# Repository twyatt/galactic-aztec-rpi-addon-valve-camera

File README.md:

# About

Custom Raspberry Pi Add-on board used for launching the [Galactic Aztec] rocket. The board was designed to be stackable with other add-on boards via the designated [pin configuration].

The Camera Control ethernet port was designed to activate [HackHD] cameras via the [Galactic Aztec Camera Control] \(rev2 or newer) board and can be configured to activate multiple [HackHD]s using the [Galactic Aztec Camera Control Splitter] board.

The Valve Feedback ethernet port was designed to read valve actuation status (open or close) by means of reading Reed switches (for the Main, LOX and Kerosene valves) via the [Galactic Aztec Reed Switch Interface] and [Galactic Aztec Reed Switch Splitter] boards.

Custom EagleCAD parts on this board can be found in the [SDSU Rocket Eagle Libraries].

## Wiring
The Camera Control and Valve Feedback ethernet ports adhered to the following [T-568B] wiring configurations:

### Camera Control
| Pin | Color        | Function |
|:---:|:------------:|:--------:|
| 1   | Orange/White | In       |
| 2   | Orange       | Out      |
| 3   | Green/White  | In       |
| 4   | Blue         | Out      |
| 5   | Blue/White   | In       |
| 6   | Green        | Out      |
| 7   | Brown/White  | In       |
| 8   | Brown        | Out      |

*In and Out do not have a polarity but rather are labeled to distinguish the two sides of the camera connection (used to [control the HackHD] by means of connecting `Button Input` to `Ground`).*

### Valve Feedback
| Pin | Color        | Function |
|:---:|:------------:|:--------:|
| 1   | Orange/White | Main     |
| 2   | Orange       | Main     |
| 3   | Green/White  | LOX      |
| 4   | Blue         | 3.3V     |
| 5   | Blue/White   | 3.3V     |
| 6   | Green        | LOX      |
| 7   | Brown/White  | Kerosene |
| 8   | Brown        | Kerosene |

# Bill of Materials
| Qty | Description                             | Part Number          | Vendor   |
|:---:|-----------------------------------------|---------------------:|----------|
| 1   | Header Stacking 2x20 Tall 23mm          | [1979]               | Adafruit |
| 2   | Jack RJ45 CAT5/CAT5e                    | [380-1046-ND]        | DigiKey  |
| 2   | Header JST PH 2mm 2-pos Right Angle PTH | [455-1719-ND]        | DigiKey  |
| 1   | LED Red Vf=1.8V If=2mA 0603             | [475-1195-2-ND]      | DigiKey  |
| 1   | Molex Mini Fit Jr. 4-pos Right Angle    | [WM1352-ND]          | DigiKey  |
| 1   | LED Red Vf=2V If=20mA 0603              | [754-1359-1-ND]      | DigiKey  |
| 3   | Transistor NPN 40V 600mA SOT-23-3       | [MMBT2222ATPMSCT-ND] | DigiKey  |
| 1   | Resistor 1.8kΩ 1/4W 1% 0603             | [P1.8KBYCT-ND]       | DigiKey  |
| 1   | Resistor 1.2kΩ 2W 1% 2512               | [A116034CT-ND]       | DigiKey  |
| 3   | Resistor 1kΩ 1/4W 1% 0603               | [RHM1.00KADCT-ND]    | DigiKey  |
| 3   | Diode 50V 1A SOD-123                    | [SM4001PL-TPMSCT-ND] | DigiKey  |
| 3   | Relay 5V 5A SPST-NO (1 Form A)          | [Z945-ND]            | DigiKey  |

[Galactic Aztec]: http://rocket.sdsu.edu/rockets
[pin configuration]: https://docs.google.com/spreadsheets/d/1zGslKhH-ZteeA8sbbTjQlF-Neb-wJ3quIlFH6I8Cvgs/edit?usp=sharing
[HackHD]: http://hackhd.com/
[Galactic Aztec Camera Control]: https://github.com/twyatt/galactic-aztec-camera-control
[Galactic Aztec Camera Control Splitter]: https://github.com/twyatt/galactic-aztec-camera-control-splitter
[Galactic Aztec Reed Switch Interface]: https://github.com/twyatt/galactic-aztec-reed-switch-interface
[Galactic Aztec Reed Switch Splitter]: https://github.com/twyatt/galactic-aztec-reed-switch-splitter
[SDSU Rocket Eagle Libraries]: https://github.com/twyatt/SDSURocket-Eagle-Libraries
[T-568B]: https://en.wikipedia.org/wiki/TIA/EIA-568#Wiring
[control the HackHD]: http://www.hackhd.com/hiw.php
[1979]: http://www.adafruit.com/products/1979
[380-1046-ND]: http://www.digikey.com/product-detail/en/SS-7188-NF/380-1046-ND/388308
[455-1719-ND]: http://www.digikey.com/product-detail/en/S2B-PH-K-S(LF)(SN)/455-1719-ND/926626
[475-1195-2-ND]: http://www.digikey.com/product-detail/en/LS%20L29K-H1J2-1-Z/475-1195-1-ND/810356
[WM1352-ND]: http://www.digikey.com/product-search/en?x=0&y=0&lang=en&site=us&keywords=538-39-30-1040
[754-1359-1-ND]: http://www.digikey.com/product-detail/en/APG1608SURKC%2FT/754-1359-1-ND/1919171
[MMBT2222ATPMSCT-ND]: http://www.digikey.com/product-detail/en/MMBT2222A-TP/MMBT2222ATPMSCT-ND/717394
[P1.8KBYCT-ND]: http://www.digikey.com/product-detail/en/ERJ-PA3F1801V/P1.8KBYCT-ND/5036145
[A116034CT-ND]: http://www.digikey.com/product-detail/en/5-2176070-1/A116034CT-ND/4280086
[RHM1.00KADCT-ND]: http://www.digikey.com/product-detail/en/ESR03EZPF1001/RHM1.00KADCT-ND/1983752
[SM4001PL-TPMSCT-ND]: http://www.digikey.com/product-detail/en/SM4001PL-TP/SM4001PL-TPMSCT-ND/1793403
[Z945-ND]: http://www.digikey.com/product-detail/en/G6B-1114P-US-DC5/Z945-ND/148724

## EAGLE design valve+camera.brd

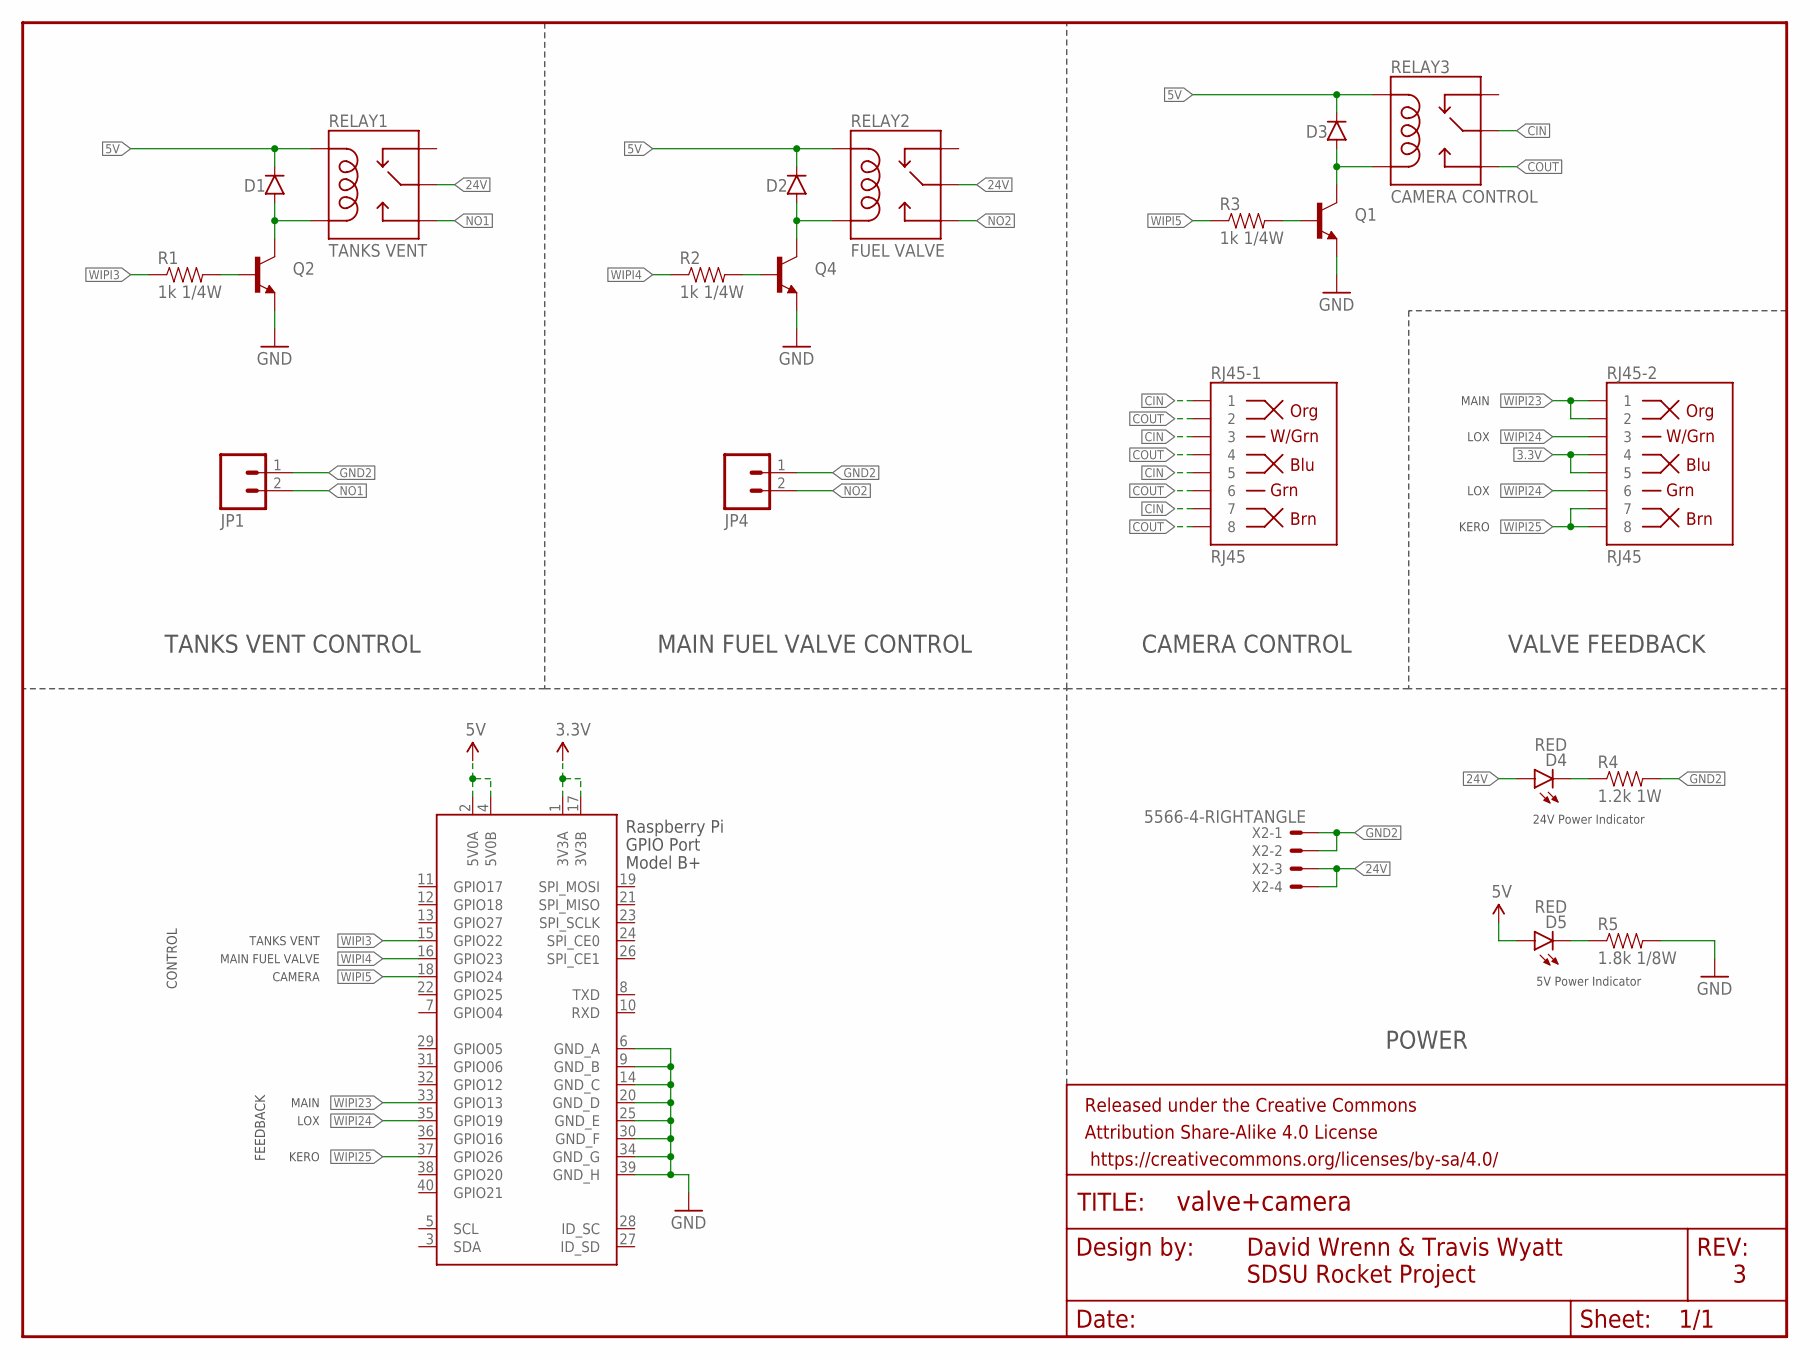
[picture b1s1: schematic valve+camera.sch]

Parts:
D1, D2, D3: DIODESOD123; SOD-123
D4, D5: RED; LED-0603
FRAME1: FRAME-LETTER; CREATIVE_COMMONS
JP1, JP4: M02-JST-2-PTH-NO_SILK; JST-2-PTH-NS
Q1, Q2, Q4: TRANSISTOR_NPNSOT23-3; SOT23-3
R1, R2, R3: 1k 1/4W; 0603-RES
R4: 1.2k 1W; R2512
R5: 1.8k 1/8W; 0603-RES
RELAY1: TANKS VENT; RELAY-G5Q
RELAY2: FUEL VALVE; RELAY-G5Q
RELAY3: CAMERA CONTROL; RELAY-G5Q
RJ45-1, RJ45-2: RJ45; RJ45-8
X1: RASPI_BOARD_B+#_H; RASPI_BOARD_B+HAT
X2: 5566-4-RIGHTANGLE; 5566-4

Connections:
3.3V: RJ45-2.4, RJ45-2.5, X1.1 (3V3A), X1.17 (3V3B)
5V: D1.C, D2.C, D3.C, D5.A, RELAY1.5 (COIL1), RELAY2.5 (COIL1), RELAY3.5 (COIL1), X1.2 (5V0A), X1.4 (5V0B)
24V: D4.A, RELAY1.2 (MAIN), RELAY2.2 (MAIN), X2.3, X2.4
CIN: RELAY3.2 (MAIN), RJ45-1.1, RJ45-1.3, RJ45-1.5, RJ45-1.7
COUT: RELAY3.3 (NO), RJ45-1.2, RJ45-1.4, RJ45-1.6, RJ45-1.8
GND: Q1.2 (E), Q2.2 (E), Q4.2 (E), R5.2, X1.6 (GND_A), X1.9 (GND_B), X1.14 (GND_C), X1.20 (GND_D), X1.25 (GND_E), X1.30 (GND_F), X1.34 (GND_G), X1.39 (GND_H)
GND2: JP1.1, JP4.1, R4.2, X2.1, X2.2
unnamed: D4.C, R4.1
unnamed: D5.C, R5.1
unnamed: Q2.1 (B), R1.2
unnamed: D1.A, Q2.3 (C), RELAY1.1 (COIL2)
unnamed: Q1.1 (B), R3.2
unnamed: D3.A, Q1.3 (C), RELAY3.1 (COIL2)
unnamed: Q4.1 (B), R2.2
unnamed: D2.A, Q4.3 (C), RELAY2.1 (COIL2)
NO1: JP1.2, RELAY1.3 (NO)
NO2: JP4.2, RELAY2.3 (NO)
WIPI3: R1.1, X1.15 (GPIO22)
WIPI4: R2.1, X1.16 (GPIO23)
WIPI5: R3.1, X1.18 (GPIO24)
WIPI23: RJ45-2.1, RJ45-2.2, X1.33 (GPIO13)
WIPI24: RJ45-2.3, RJ45-2.6, X1.35 (GPIO19)
WIPI25: RJ45-2.7, RJ45-2.8, X1.37 (GPIO26)

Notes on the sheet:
CAMERA CONTROL
POWER
David Wrenn & Travis Wyatt
SDSU Rocket Project
24V Power Indicator
5V Power Indicator
VALVE FEEDBACK
TANKS VENT CONTROL
MAIN FUEL VALVE CONTROL
LOX
MAIN
KERO
TANKS VENT
MAIN FUEL VALVE
CAMERA
CONTROL
FEEDBACK

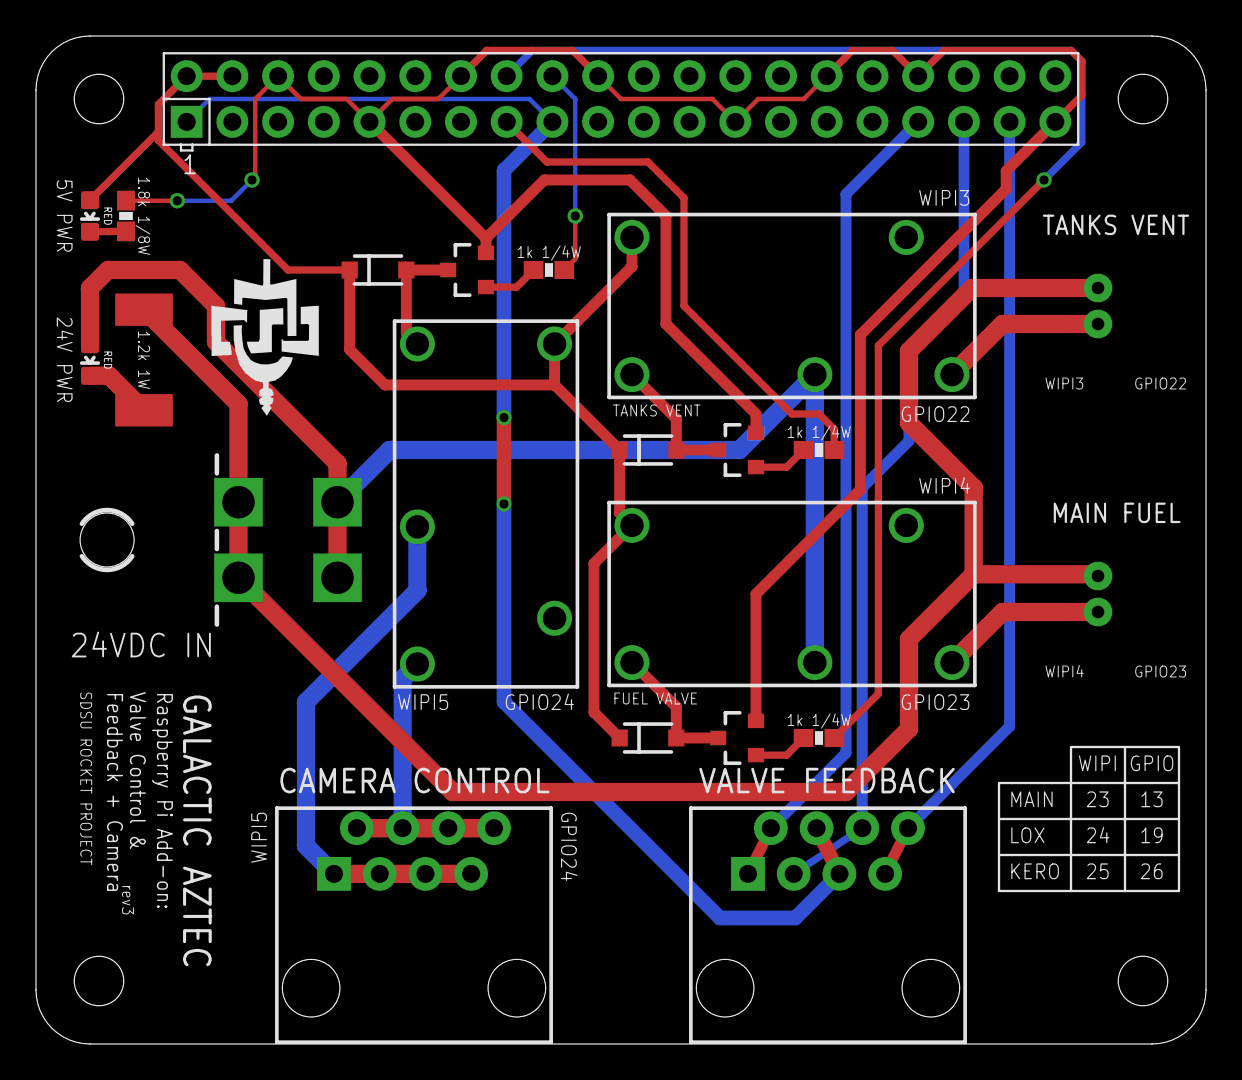
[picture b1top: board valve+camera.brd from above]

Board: 2 copper layers, 65.0 x 56.0 mm, 23 parts (0 on the bottom side), 23 nets.

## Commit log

2015-07-30 Update camera control wiring and relay components
    Updated the components driving the relays to be SMD rather than PTH.
    The camera control wiring was updated to have relay activating HackHDs
    to be located on this board rather than being located on each Camera
    Control board (this means that this board is no longer compatible with
    rev1 of the Camera Control board and now requires rev2 or newer).
2015-07-31 Fix feedback port and power thru hole size
    Feedback ethernet port was fixed by adding a missing trace.
    The 24VDC in thru hole size diameter was increased to adhere to the
    datasheet's specifications.
    The JST plugs used for valve actuation (tanks vent and main fuel) were
    change from SMD to PTH as we had problems with the SMD connectors
    breaking off when connecting or disconnecting the plugs.

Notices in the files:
parts and their libraries:
SparkFun-Connectors: Licensing: Creative Commons ShareAlike 4.0 International - https://creativecommons.org/licenses/by-sa/4.0
SparkFun-Aesthetics: Released under the Creative Commons Attribution Share-Alike 4.0 License
SparkFun-Aesthetics: https://creativecommons.org/licenses/by-sa/4.0
